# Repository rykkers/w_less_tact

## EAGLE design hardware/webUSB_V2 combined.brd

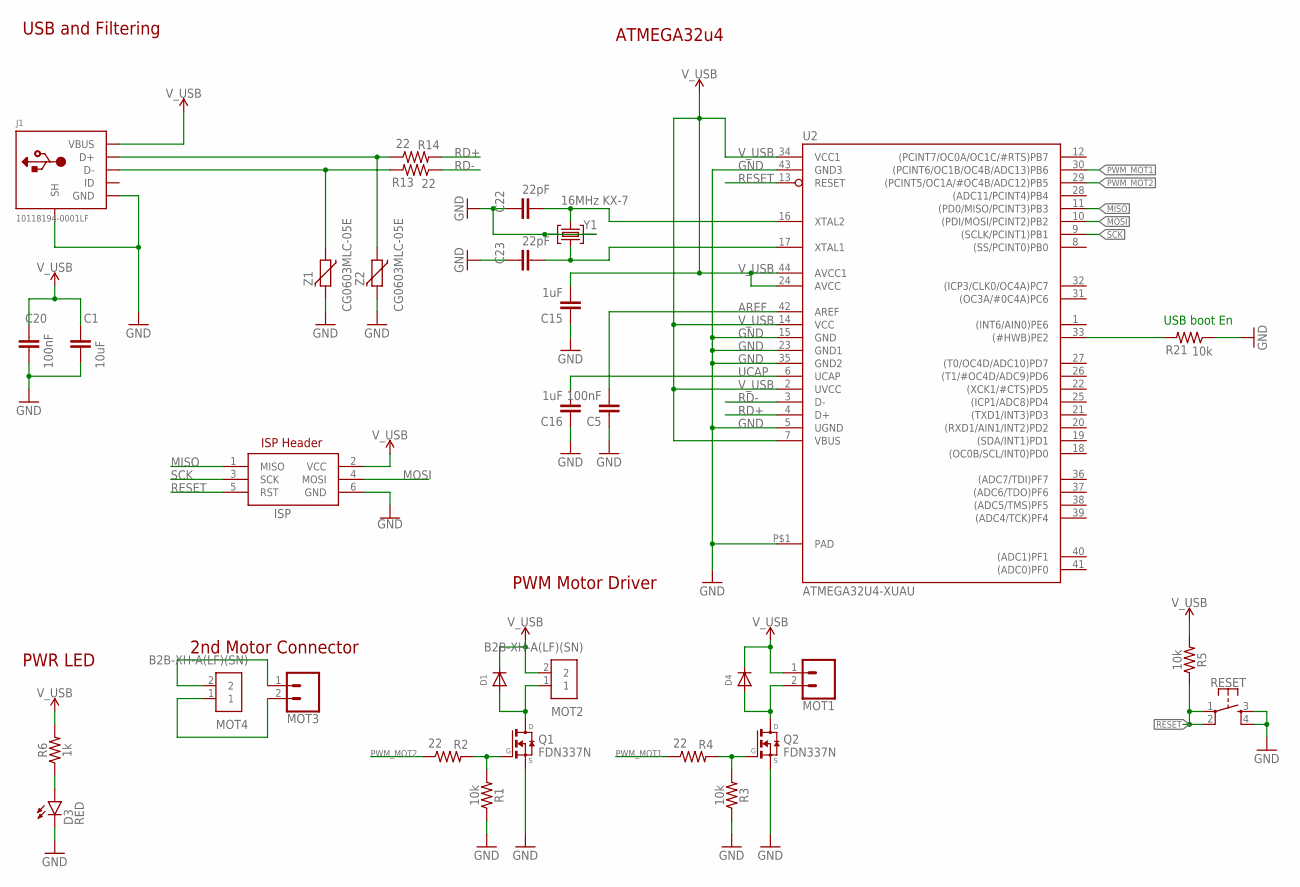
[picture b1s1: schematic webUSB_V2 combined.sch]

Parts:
C1: 10uF; C0805
C5, C20: 100nF; C0603
C15, C16: 1uF; C0603
C22, C23: 22pF; C0603
D1, D4: DIODESOD-123; SOD-123
D3: RED; LED-0603
ISP: AVRISP-6; AVRISP
J1: 10118194-0001LF; FRAMATOME_10118194-0001LF
MOT1, MOT3: CONN_02; 1X02
MOT2, MOT4: B2B-XH-A(LF)(SN); SHDR2W64P0X250_1X2_740X575X700
Q1, Q2: FDN337N; SSOT-3
R1, R3, R5, R21: 10k; R0603
R2, R4, R13, R14: 22; R0603
R6: 1k; R0603
RESET: TACTILE_BUTTON_PTS810; PTS810
U2: ATMEGA32U4-XUAU; TQFP44-PAD
Y1: 16MHz KX-7; CRYSTAL-3.2-2.5
Z1, Z2: CG0603MLC-05E; CT/CN0603

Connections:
AREF: C5.2, U2.42 (AREF)
D+: J1.D+, R14.1, Z2.1
D-: J1.D-, R13.2, Z1.1
GND: C1.1, C5.1, C15.1, C16.1, C20.1, C22.2, C23.2, D3.C, ISP.6 (GND), J1.GND, J1.SH1 (SH), J1.SH2 (SH), J1.SH3 (SH), J1.SH4 (SH), J1.SH5 (SH), J1.SH6 (SH), J1.SH7 (SH), J1.SH8 (SH), Q1.2 (S), Q2.2 (S), R1.1, R3.1, R21.1, RESET.3, RESET.4, U2.5 (UGND), U2.15 (GND), U2.23 (GND1), U2.35 (GND2), U2.43 (GND3), U2.P$1 (PAD), Y1.2 (GND), Y1.4 (GND), Z1.2, Z2.2
HWB: R21.2, U2.33 ((#HWB)PE2)
MISO: ISP.1 (MISO), U2.11 ((PD0/MISO/PCINT3)PB3)
MOSI: ISP.4 (MOSI), U2.10 ((PDI/MOSI/PCINT2)PB2)
unnamed: Q1.1 (G), R1.2, R2.2
unnamed: D1.A, MOT2.1, Q1.3 (D)
unnamed: D4.A, MOT1.2, Q2.3 (D)
unnamed: Q2.1 (G), R3.2, R4.2
unnamed: MOT3.1, MOT4.2
unnamed: MOT3.2, MOT4.1
unnamed: D3.A, R6.1
PWM_MOT1: R4.1, U2.30 ((PCINT6/OC1B/OC4B/ADC13)PB6)
PWM_MOT2: R2.1, U2.29 ((PCINT5/OC1A/#OC4B/ADC12)PB5)
RD+: R14.2, U2.4 (D+)
RD-: R13.1, U2.3 (D-)
RESET: ISP.5 (RST), R5.1, RESET.1, RESET.2, U2.13 (RESET)
SCK: ISP.3 (SCK), U2.9 ((SCLK/PCINT1)PB1)
UCAP: C16.2, U2.6 (UCAP)
V_USB: C1.2, C15.2, C20.2, D1.C, D4.C, ISP.2 (VCC), J1.VUSB (VBUS), MOT1.1, MOT2.2, R5.2, R6.2, U2.2 (UVCC), U2.7 (VBUS), U2.14 (VCC), U2.24 (AVCC), U2.34 (VCC1), U2.44 (AVCC1)
XTAL3: C22.1, U2.16 (XTAL2), Y1.3 (C2)
XTAL4: C23.1, U2.17 (XTAL1), Y1.1 (C1)

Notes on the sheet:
USB and Filtering
PWR LED
PWM Motor Driver
2nd Motor Connector
USB boot En
ISP Header
ATMEGA32u4

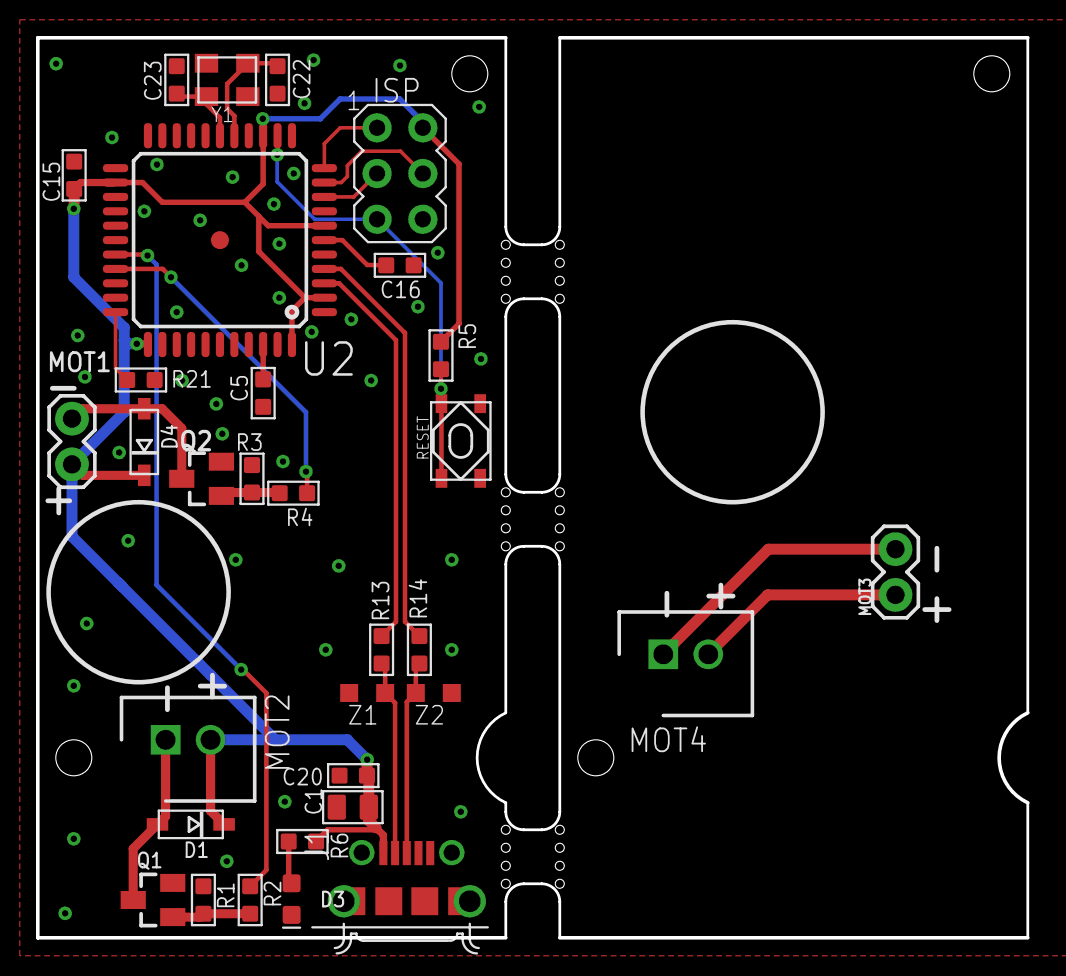
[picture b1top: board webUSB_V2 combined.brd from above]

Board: 2 copper layers, 55.0 x 50.0 mm, 32 parts (0 on the bottom side), 24 nets.

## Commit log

2021-05-05 added schematic file and firmware
2021-05-17 made sure brd file was added to commits

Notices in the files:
parts and their libraries:
SparkFun-LED: Licensing: Creative Commons ShareAlike 4.0 International - https://creativecommons.org/licenses/by-sa/4.0
